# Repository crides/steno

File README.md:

# Steno

If you are here, you are probably looking for my embedded steno work. You can find the PCB design and production files for my steno keyboards (mostly known as the batwing or just bat) in the `pcb/` directory, and the embedded steno firmware (Kolibri) and the dictionary compiler in the `firmware/` and `compiler/` directories.

The detailed info for each can be found in their own READMEs, [boards](pcb/README.md) [firmware](firmware/README.md) and [dictionary compiler](compiler/README.md).

## What's Steno(graphy)?

If you don't know what stenography is, it's a short hand system primarily used by court reporters and captioners for note taking at a very high speeds. The English stenography system uses a special keyboard with only 23 keys on it, and the keys are meant to be pressed at the same time, producing combinations called chords. When combined together and translated through an engine, it can be used to input at very high speeds (professional stenographers need to reach above 225 wpm). Due to the price of commercial steno machines, free and open source alternatives started appearing, the most prominent among which is [Plover](https://github.com/openstenoproject/plover), which acts as a keyboard emulator that can translate chords from a \$20 gaming keyboard into words efficiently. A lot of ideas here are inspired by Plover.

If you want to go a bit more in depth, you should check out [this video](https://www.youtube.com/watch?v=JsRTTD9k2ME) by Aerick, or this [PyCon talk](https://www.youtube.com/watch?v=Wpv-Qb-dB6g) by Mirabai Knight, the creator of Plover.

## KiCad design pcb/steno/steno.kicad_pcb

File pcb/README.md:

# Embedded steno boards

These are the steno keyboards I designed and built, almost all of which has some form of hardware support for a embedded steno engine. These are just a list for more or less steno centric designs though, you can find my other boards using embedded steno like the [fissure v3](https://github.com/crides/fissure) and the [fusion](https://github.com/crides/fusion).

## Version 4

Version 4 is/are being designed as a more general board for others to use. There have been some people in the community requested me to sell some form of embedded steno board, and hardware vendors have yet to integrate the system (which on hardware is at least a flash chip). So these design(s) are meant to be easier to manufacture or assemble for the people printing their own.

## Version 3b / Bluebat

Picture from Jen/@sammdot: 

This is the screen testing platform for future designs with BLE versions of the bat. It was meant to compare the characteristics and power consumption of OLEDs, Eink display, Sharp memory display and the 2.2 inch LCD used in version 2 & 3. This version is not actually open sourced, as it was meant to simply be a personal testing board. The only reason it's here is because one was built for Jen/@sammdot as she requested one bat for polishing the UI (and the ATMega32u4 based ones, i.e. all previous versions, don't have enough flash for a good UI to be built without compromising other features).

## Version 3

Version 3 is the public testing version. This is done so that I can get more feedback from the community. This version uses basically the same design from version 2, but adopts a [raw screen module](https://www.aliexpress.com/item/32417585937.html) so that the cost of building is much cheaper. The other components are pushed to the back of the board as I imagine there wouldn't be much room at the front. This caused me a bit of trouble as I still want to put the diodes for the switches at the front, underneath the switches so that they are hidden. But that means I needed to hand solder the diodes while the other components are assembled at JLCPCB (they only support one sided assembly). As this was a public version, I changed the stagger of the keyboard to mimic that of Georgi's, but retained the relative position between thumbs and fingers (specifically thumb home and index home).

This version has been sent out to 9 other testers (I have one for testing) which helped me fix the dictionary downloader and polish the dictionary editing interface a bit more.

## Version 2

Version 2 is the one done as a class project (ECE445, Senior Project Labotory) and you can see the class number as a branch containing the work done there (it's been merged a long time ago of course). This is also the point where I ask the community for a name of the board, and that's where BatWings (or simply bat) comes from, from a suggestion by Jane/Germ/HardAsMagnets.

The main difference of this version is that it embeds the MCU onto the board itself (per course hardware requirements), includes a [much larger screen](https://www.adafruit.com/product/1480), and starts to use Bezier curves all over the board. Note that the one pictured is the first revision where the design is not electrically sound: I forgot a level shifter for the 5V MCU to interface with a 3.3V flash. This was not a problem before as the feather I was using runs the MCU at 3.3V and 8MHz. You could see the bodge wires under the screen if you look closely

This is also the point where me and my team added command formats so that the firmware can start to support a larger portion of Plover's builtin commands, and changed the dictionary format to a simpler and more regular one based on a single level of hashmap.

## Stenophone

This is a experimental version aimed to bring hardware steno to phones, so that one might be able to steno on the go (like on the bus, generally when you don't have a place to sit down). The idea is that you put this keyboard on the back of your phone, and your fingers reach to the back to press the keys, and your thumb will go over the phone to reach the vowels. This version is really only for testing out the idea, therefore a lot of the design aspects are still incomplete (for example see the battery location on the back). This version only differs in layout compare to the other ones, and uses the same steno firmware. It still uses BLE, as the plug on the phone will be simply blocked by hands.

## Version 1

Version 1 is a much better improvement over the first. This time I chose a split layout, but on the same board so I may use it on the go. The 2 halves are rotated 20 degrees each, so my hands won't have to bend much since it's not a actual split board. Like [my split keyboard](https://github.com/crides/fissure), this version also includes high levels of columnar stagger. I also put the MCU back to a normal position, so I don't have to worry about the underside of the keyboard anymore. This version also added a JST Li-ion battery plug (although in a weird position), a OLED for status display, a SOIC8 for experimenting with a QSPI flash, and a sdcard slot under the OLED screen.

Note the location of the sdcard; this is when it's not properly inserted to show the location. Also note the weirdly large battery and JST plug location.

## Version 0

The version 0 board is just a experimental board, with a small form factor while keeping the 11 column of keys needed. The number bar is missing, just like the Georgi, and the number keys are placed at either side of the vowels. As I was just starting to practice steno, I didn't know much about the dimension of a steno keyboard that I would feel comfortable using, so I simply used a ortholinear layout. In order to keep the form factor small, I tried to put the MCU under the PCB, so that it doesn't take any extra space on the PCB itself. But since I'm not used to doing that, it caused some issues when I later tried to modify the board and in normal usage.

Note the candy boxes I used to lift the board up so it's stable. Also note the sdcard slot and the bodges I did to accomodate the dictionary in the firmware.

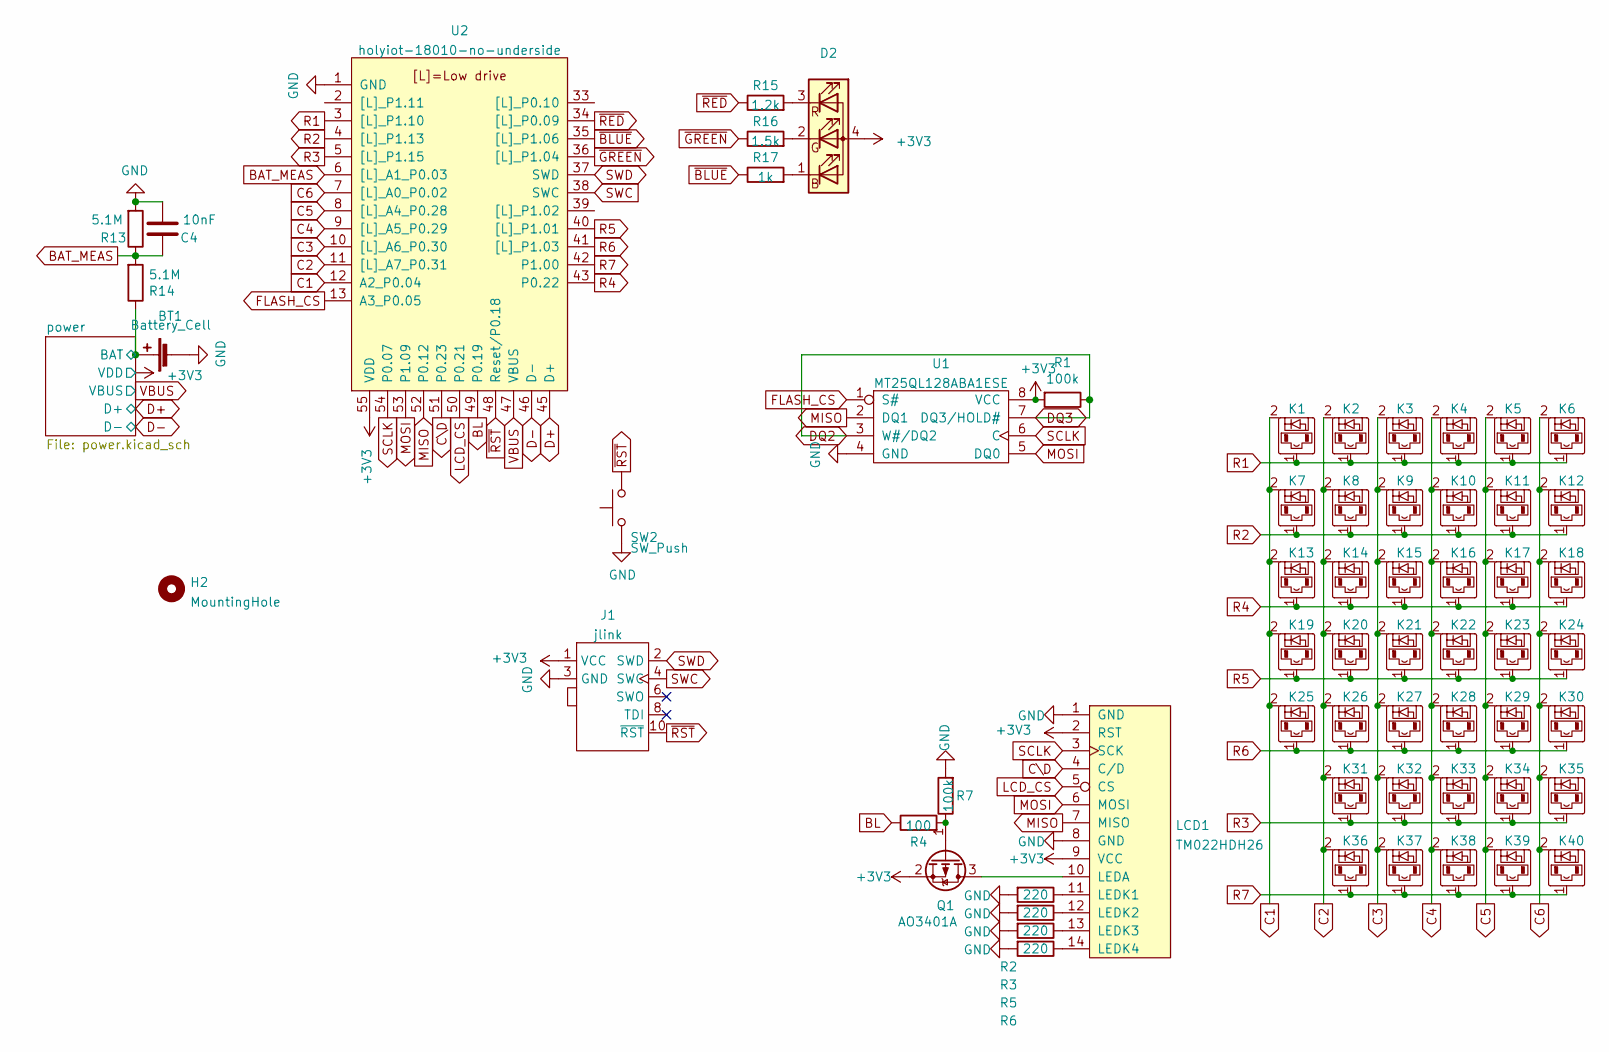
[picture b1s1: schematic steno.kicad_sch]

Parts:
BT1: Battery_Cell; JST_PH_S2B-PH-SM4-TB_1x02-1MP_P2.00mm_Horizontal
C4: 10nF; C_0603_1608Metric
D2: (no value)
H2: MountingHole; auklet-cover-mount
J1: jlink; PinHeader_2x05_P1.27mm_Vertical_SMD
K1, K2, K3, K4, K5, K6, K7, K8, K9, K10, K11, K12, K13, K14, K15, K16, K17, K18, K19, K20, K21, K22, K23, K24, K25, K26, K27, K28, K29, K30, K31, K32, K33, K34, K35, K36, K37, K38, K39, K40: diode-choc; pg1350-D
LCD1: TM022HDH26; TM022HDH26_back
Q1: AO3401A; SOT-23
R1, R7: 100k; R_0603_1608Metric
R2, R3, R5, R6: 220; R_0603_1608Metric
R4: 100; R_0603_1608Metric
R13, R14: 5.1M; R_0603_1608Metric
R15: 1.2k; R_0603_1608Metric
R16: 1.5k; R_0603_1608Metric
R17: 1k; R_0603_1608Metric
SW2: SW_Push; SW_SPST_TL3342
U1: MT25QL128ABA1ESE; SOIC-8_5.23x5.23mm_P1.27mm
U2: holyiot-18010-no-underside

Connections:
+3V3: D2.4 (A), J1.1 (VCC), LCD1.2 (RST), LCD1.9 (VCC), Q1.2 (S), R1.2, U1.8 (VCC), U2.55 (VDD); also elsewhere on the board
/power/BAT: BT1.1 (+), R14.1; also elsewhere on the board
BAT_MEAS: C4.1, R13.1, R14.2, U2.6 ([L]_A1_P0.03)
BL: R4.1, U2.49 (P0.19)
C1: K1.2, K7.2, K13.2, K19.2, K25.2, U2.12 (A2_P0.04)
C2: K2.2, K8.2, K14.2, K20.2, K26.2, K31.2, K36.2, U2.11 ([L]_A7_P0.31)
C3: K3.2, K9.2, K15.2, K21.2, K27.2, K32.2, K37.2, U2.10 ([L]_A6_P0.30)
C4: K4.2, K10.2, K16.2, K22.2, K28.2, K33.2, K38.2, U2.9 ([L]_A5_P0.29)
C5: K5.2, K11.2, K17.2, K23.2, K29.2, K34.2, K39.2, U2.8 ([L]_A4_P0.28)
C6: K6.2, K12.2, K18.2, K24.2, K30.2, K35.2, K40.2, U2.7 ([L]_A0_P0.02)
C\D: LCD1.4 (C/D), U2.51 (P0.23)
D+: U2.45 (D+); also elsewhere on the board
D-: U2.46 (D-); also elsewhere on the board
DQ2: R1.1, U1.3 (W#/DQ2), U1.7 (DQ3/HOLD#)
FLASH_CS: U1.1 (S#), U2.13 (A3_P0.05)
GND: BT1.2 (-), C4.2, J1.3 (GND), J1.5 (GND), LCD1.1 (GND), LCD1.8 (GND), R2.2, R3.2, R5.2, R6.2, R7.2, R13.2, SW2.1, U1.4 (GND), U2.1 (GND), U2.32 (GND), U2.44 (GND); also elsewhere on the board
LCD_CS: LCD1.5 (CS), U2.50 (P0.21)
MISO: LCD1.7 (MISO), U1.2 (DQ1), U2.52 (P0.12)
MOSI: LCD1.6 (MOSI), U1.5 (DQ0), U2.53 (P1.09)
unnamed: LCD1.10 (LEDA), Q1.3 (D)
unnamed: LCD1.11 (LEDK1), R2.1
unnamed: LCD1.12 (LEDK2), R3.1
unnamed: LCD1.13 (LEDK3), R5.1
unnamed: LCD1.14 (LEDK4), R6.1
unnamed: Q1.1 (G), R4.2, R7.1
unnamed: D2.3 (RK), R15.2
unnamed: D2.2 (GK), R16.2
unnamed: D2.1 (BK), R17.2
R1: K1.1, K2.1, K3.1, K4.1, K5.1, K6.1, U2.3 ([L]_P1.10)
R2: K7.1, K8.1, K9.1, K10.1, K11.1, K12.1, U2.4 ([L]_P1.13)
R3: K31.1, K32.1, K33.1, K34.1, K35.1, U2.5 ([L]_P1.15)
R4: K13.1, K14.1, K15.1, K16.1, K17.1, K18.1, U2.43 (P0.22)
R5: K19.1, K20.1, K21.1, K22.1, K23.1, K24.1, U2.40 ([L]_P1.01)
R6: K25.1, K26.1, K27.1, K28.1, K29.1, K30.1, U2.41 ([L]_P1.03)
R7: K36.1, K37.1, K38.1, K39.1, K40.1, U2.42 (P1.00)
SCLK: LCD1.3 (SCK), U1.6 (C), U2.54 (P0.07)
SWC: J1.4 (SWC), U2.38 (SWC)
SWD: J1.2 (SWD), U2.37 (SWD)
VBUS: U2.47 (VBUS); also elsewhere on the board
~BLUE: R17.1, U2.35 ([L]_P1.06)
~GREEN: R16.1, U2.36 ([L]_P1.04)
~RED: R15.1, U2.34 ([L]_P0.09)
~RST: J1.10 (~RST), SW2.2, U2.48 (Reset/P0.18)

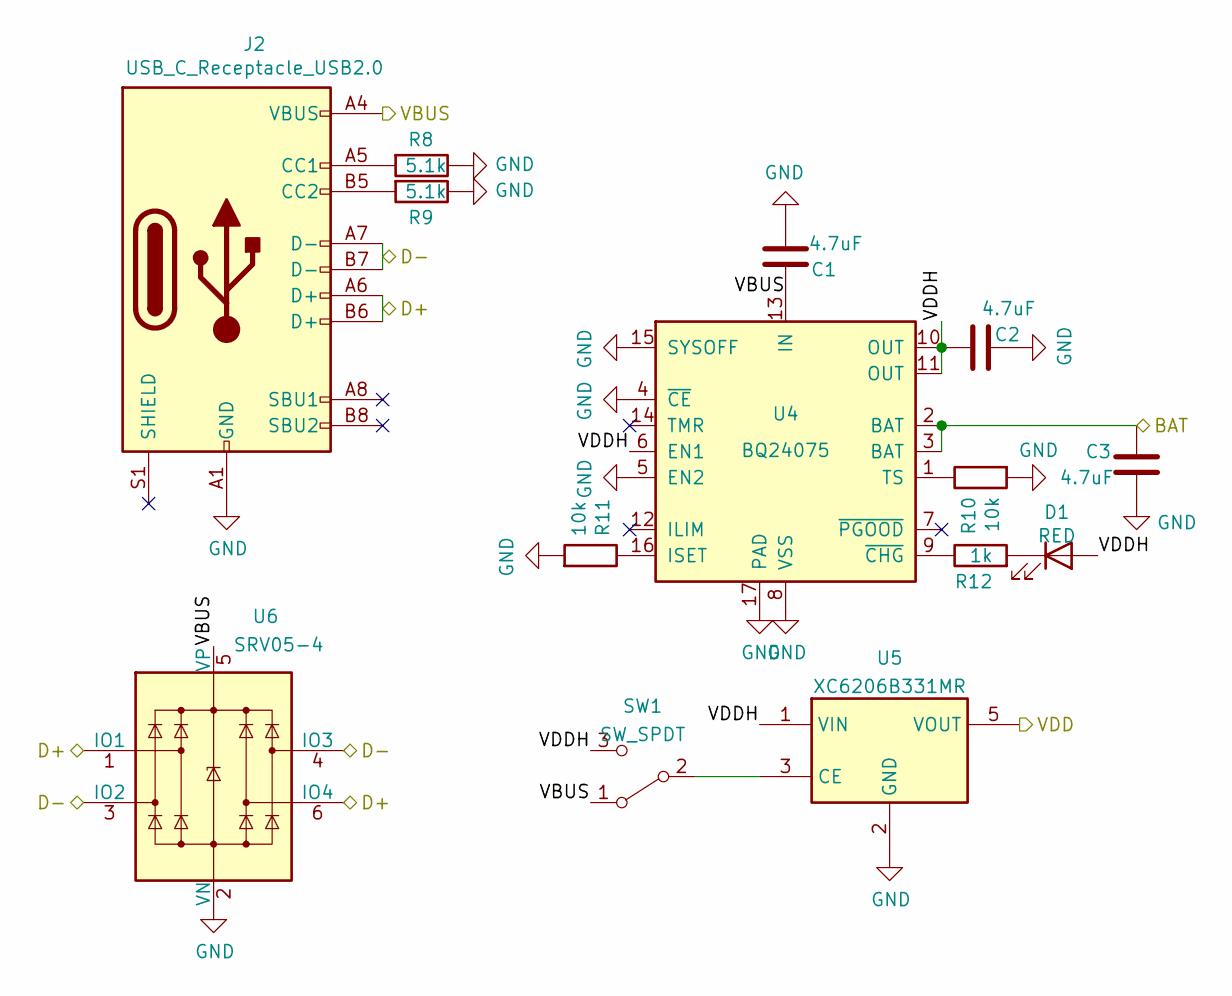
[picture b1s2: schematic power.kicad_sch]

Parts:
C1, C2, C3: 4.7uF; C_0603_1608Metric
D1: RED; LED_0805_2012Metric
J2: USB_C_Receptacle_USB2.0; USB_C_Receptacle_HRO_TYPE-C-31-M-12
R8, R9: 5.1k; R_0603_1608Metric
R10, R11: 10k; R_0603_1608Metric
R12: 1k; R_0603_1608Metric
SW1: SW_SPDT; SW_SPDT_PCM12
U4: BQ24075; VQFN-16-1EP_3x3mm_P0.5mm_EP1.68x1.68mm_ThermalVias
U5: XC6206B331MR; SOT-23-5
U6: SRV05-4; SOT-23-6

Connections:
+3V3: U5.5 (VOUT); also elsewhere on the board
/power/BAT: C3.1, U4.2 (BAT), U4.3 (BAT); also elsewhere on the board
/power/VDDH: C2.2, D1.2 (A), SW1.3 (C), U4.6 (EN1), U4.10 (OUT), U4.11 (OUT), U5.1 (VIN)
D+: J2.A6 (D+), J2.B6 (D+), U6.1 (IO1), U6.6 (IO4); also elsewhere on the board
D-: J2.A7 (D-), J2.B7 (D-), U6.3 (IO2), U6.4 (IO3); also elsewhere on the board
GND: C1.2, C2.1, C3.2, J2.A1 (GND), J2.A12 (GND), J2.B1 (GND), J2.B12 (GND), R8.1, R9.1, R10.2, R11.2, U4.4 (~CE), U4.5 (EN2), U4.8 (VSS), U4.15 (SYSOFF), U4.17 (PAD), U5.2 (GND), U6.2 (VN); also elsewhere on the board
unnamed: D1.1 (K), R12.2
unnamed: J2.A5 (CC1), R8.2
unnamed: J2.B5 (CC2), R9.2
unnamed: R10.1, U4.1 (TS)
unnamed: R11.1, U4.16 (ISET)
unnamed: R12.1, U4.9 (~CHG)
unnamed: SW1.2 (B), U5.3 (CE)
VBUS: C1.1, J2.A4 (VBUS), J2.A9 (VBUS), J2.B4 (VBUS), J2.B9 (VBUS), SW1.1 (A), U4.13 (IN), U6.5 (VP); also elsewhere on the board

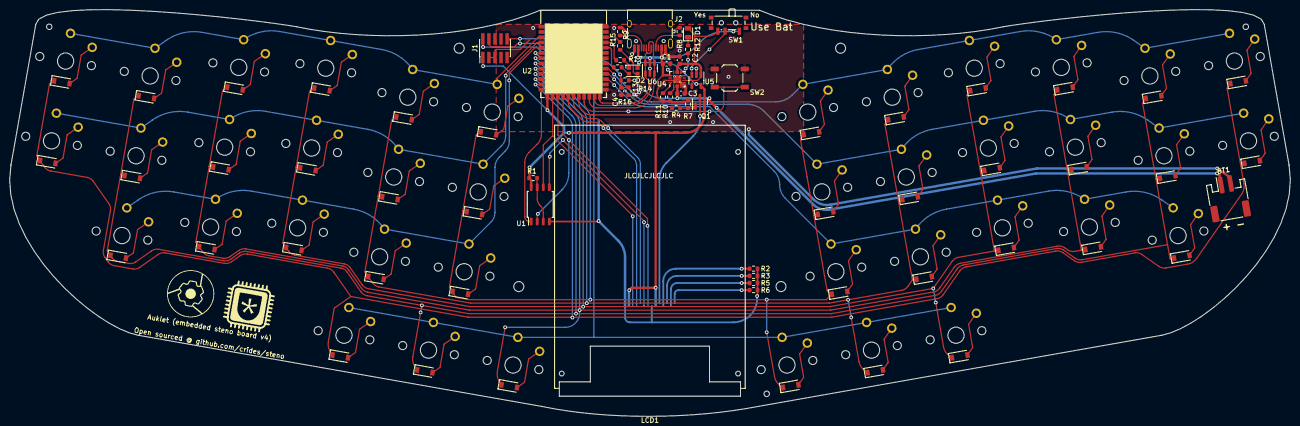
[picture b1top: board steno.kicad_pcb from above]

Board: 2 copper layers, 268.7 x 85.3 mm, 76 parts (0 on the bottom side), 51 nets.

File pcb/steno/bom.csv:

Comment,Designator,Footprint,LCSC
4.7uF,"C1,C2,C3",Capacitor_SMD:C_0603_1608Metric,
10nF,C4,Capacitor_SMD:C_0603_1608Metric,
RED,D1,LED_SMD:LED_0805_2012Metric,
LED_RABG,D2,LED_SMD:LED_ASMB-KTF0-0A306,C375569
MountingHole,H1,misc:auklet-mount,
MountingHole,H2,misc:auklet-cover-mount,
USB_C_Receptacle_USB2.0,J2,Connector_USB:USB_C_Receptacle_HRO_TYPE-C-31-M-12,
diode-choc,"K1,K2,K3,K4,K5,K6,K7,K8,K9,K10,K11,K12,K13,K14,K15,K16,K17,K18,K19,K20,K21,K22,K23,K24,K25,K26,K27,K28,K29,K30,K31,K32,K33,K34,K35,K36,K37,K38,K39,K40",pg1350:pg1350-D,C64898
AO3401A,Q1,Package_TO_SOT_SMD:SOT-23,
100k,"R1,R7",Resistor_SMD:R_0603_1608Metric,
220,"R2,R3,R5,R6",Resistor_SMD:R_0603_1608Metric,
100,R4,Resistor_SMD:R_0603_1608Metric,
5.1k,"R8,R9",Resistor_SMD:R_0603_1608Metric,
10k,"R10,R11",Resistor_SMD:R_0603_1608Metric,
1k,"R12,R17",Resistor_SMD:R_0603_1608Metric,
5.1M,"R13,R14",Resistor_SMD:R_0603_1608Metric,C13320
1.2k,R15,Resistor_SMD:R_0603_1608Metric,
1.5k,R16,Resistor_SMD:R_0603_1608Metric,
SW_SPDT,SW1,Button_Switch_SMD:SW_SPDT_PCM12,
SW_Push,SW2,Button_Switch_SMD:SW_SPST_TL3342,C318884
MT25QL128ABA1ESE,U1,Package_SO:SOIC-8_5.23x5.23mm_P1.27mm,
BQ24075,U4,Package_DFN_QFN:VQFN-16-1EP_3x3mm_P0.5mm_EP1.68x1.68mm_ThermalVias,
XC6206B331MR,U5,Package_TO_SOT_SMD:SOT-23-5,
SRV05-4,U6,Package_TO_SOT_SMD:SOT-23-6,

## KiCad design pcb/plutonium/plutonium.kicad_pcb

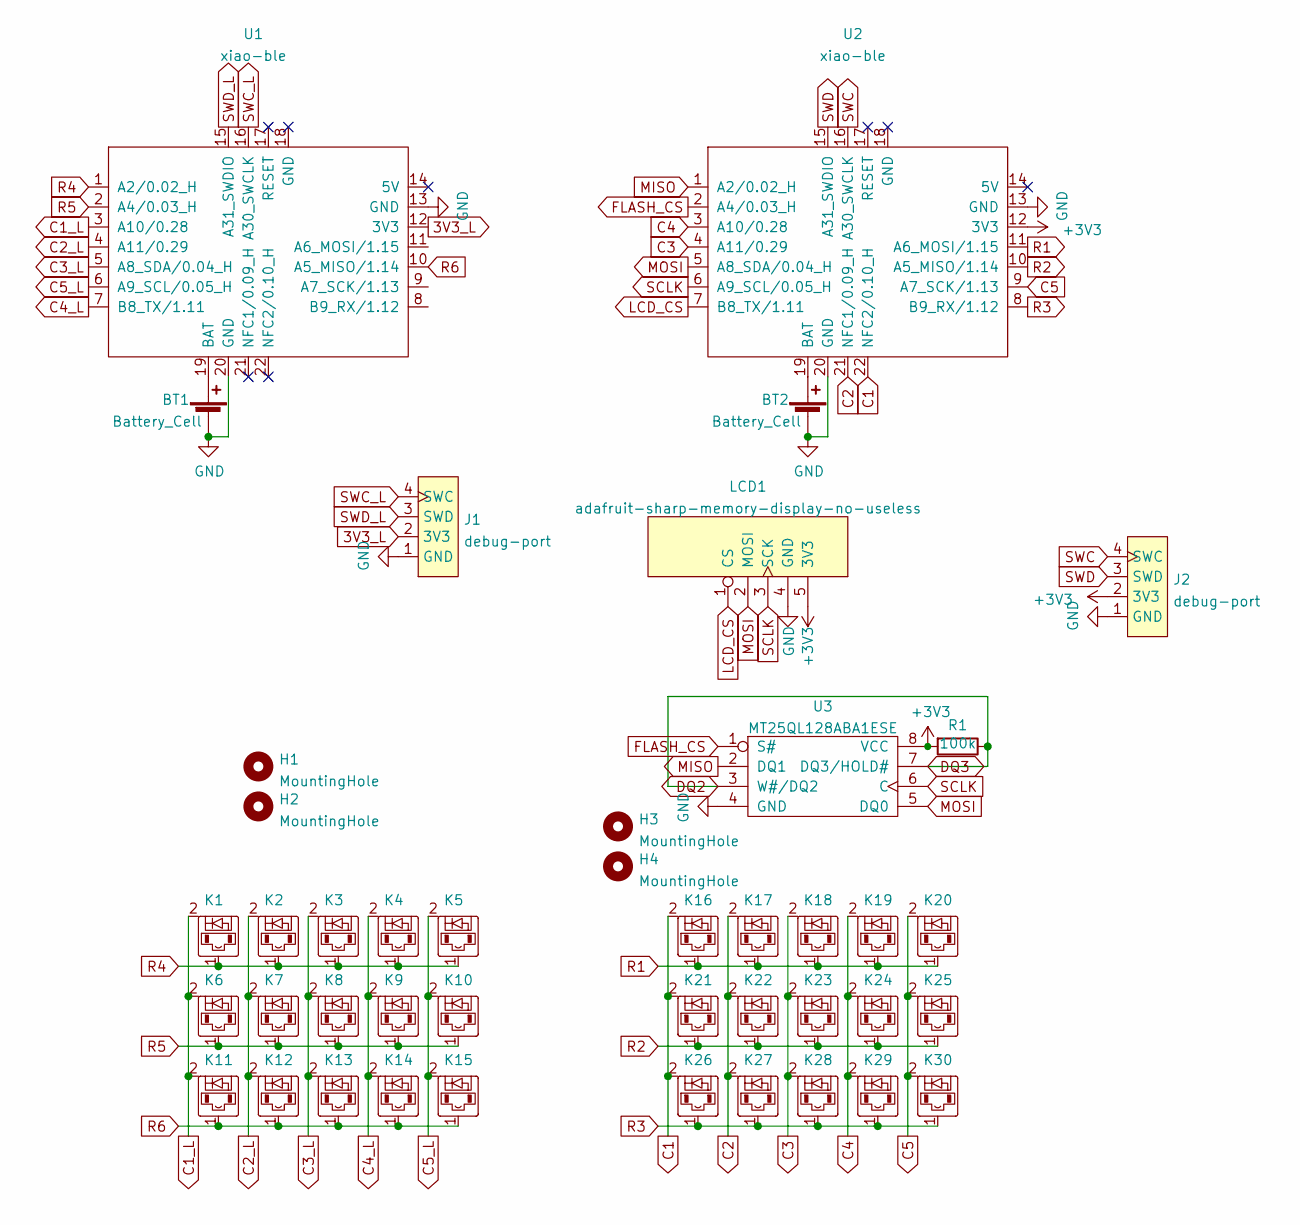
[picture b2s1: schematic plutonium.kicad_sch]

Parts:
BT1, BT2: Battery_Cell; JST_PH_S2B-PH-SM4-TB_1x02-1MP_P2.00mm_Horizontal
H1, H2, H3, H4: MountingHole; MountingHole_3.2mm_M3
J1, J2: debug-port; debug-port-single-side
K1, K2, K3, K4, K5, K6, K7, K8, K9, K10, K11, K12, K13, K14, K15, K16, K17, K18, K19, K20, K21, K22, K23, K24, K25, K26, K27, K28, K29, K30: diode-choc; pg1350-D
LCD1: adafruit-sharp-memory-display-no-useless; adafruit-sharp-memory-display-1.3in-no-mounting-no-useless
R1: 100k; R_0603_1608Metric
U1, U2: xiao-ble; xiao-ble-smd-cutout
U3: MT25QL128ABA1ESE; SOIC-8_5.23x5.23mm_P1.27mm

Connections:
3V3_L: J1.2 (3V3), U1.12 (3V3)
+3V3: J2.2 (3V3), LCD1.5 (3V3), R1.2, U2.12 (3V3), U3.8 (VCC)
C1: K16.2, K21.2, K26.2, U2.22 (NFC2/0.10_H)
C1_L: K1.2, K6.2, K11.2, U1.3 (A10/0.28)
C2: K17.2, K22.2, K27.2, U2.21 (NFC1/0.09_H)
C2_L: K2.2, K7.2, K12.2, U1.4 (A11/0.29)
C3: K18.2, K23.2, K28.2, U2.4 (A11/0.29)
C3_L: K3.2, K8.2, K13.2, U1.5 (A8_SDA/0.04_H)
C4: K19.2, K24.2, K29.2, U2.3 (A10/0.28)
C4_L: K4.2, K9.2, K14.2, U1.7 (B8_TX/1.11)
C5: K20.2, K25.2, K30.2, U2.9 (A7_SCK/1.13)
C5_L: K5.2, K10.2, K15.2, U1.6 (A9_SCL/0.05_H)
DQ2: R1.1, U3.3 (W#/DQ2), U3.7 (DQ3/HOLD#)
FLASH_CS: U2.2 (A4/0.03_H), U3.1 (S#)
GND: BT1.2 (-), BT2.2 (-), J1.1 (GND), J2.1 (GND), LCD1.4 (GND), U1.13 (GND), U1.20 (GND), U2.13 (GND), U2.20 (GND), U3.4 (GND)
LCD_CS: LCD1.1 (CS), U2.7 (B8_TX/1.11)
MISO: U2.1 (A2/0.02_H), U3.2 (DQ1)
MOSI: LCD1.2 (MOSI), U2.5 (A8_SDA/0.04_H), U3.5 (DQ0)
unnamed: BT1.1 (+), U1.19 (BAT)
unnamed: BT2.1 (+), U2.19 (BAT)
R1: K16.1, K17.1, K18.1, K19.1, K20.1, U2.11 (A6_MOSI/1.15)
R2: K21.1, K22.1, K23.1, K24.1, K25.1, U2.10 (A5_MISO/1.14)
R3: K26.1, K27.1, K28.1, K29.1, K30.1, U2.8 (B9_RX/1.12)
R4: K1.1, K2.1, K3.1, K4.1, K5.1, U1.1 (A2/0.02_H)
R5: K6.1, K7.1, K8.1, K9.1, K10.1, U1.2 (A4/0.03_H)
R6: K11.1, K12.1, K13.1, K14.1, K15.1, U1.10 (A5_MISO/1.14)
SCLK: LCD1.3 (SCK), U2.6 (A9_SCL/0.05_H), U3.6 (C)
SWC: J2.4 (SWC), U2.16 (A30_SWCLK)
SWC_L: J1.4 (SWC), U1.16 (A30_SWCLK)
SWD: J2.3 (SWD), U2.15 (A31_SWDIO)
SWD_L: J1.3 (SWD), U1.15 (A31_SWDIO)

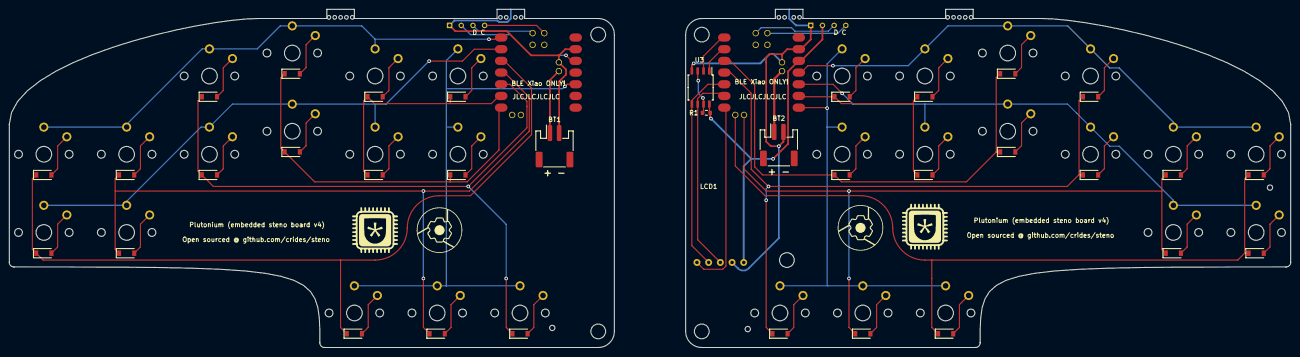
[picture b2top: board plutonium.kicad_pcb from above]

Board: 2 copper layers, 278.5 x 73.5 mm, 43 parts (0 on the bottom side), 31 nets.

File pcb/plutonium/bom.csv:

Comment,Designator,Footprint,LCSC
diode-choc,"K1,K2,K3,K4,K5,K6,K7,K8,K9,K10,K11,K12,K13,K14,K15,K16,K17,K18,K19,K20,K21,K22,K23,K24,K25,K26,K27,K28,K29,K30",pg1350:pg1350-D,C64898
100k,R1,Resistor_SMD:R_0603_1608Metric,
MT25QL128ABA1ESE,U3,Package_SO:SOIC-8_5.23x5.23mm_P1.27mm,C97521

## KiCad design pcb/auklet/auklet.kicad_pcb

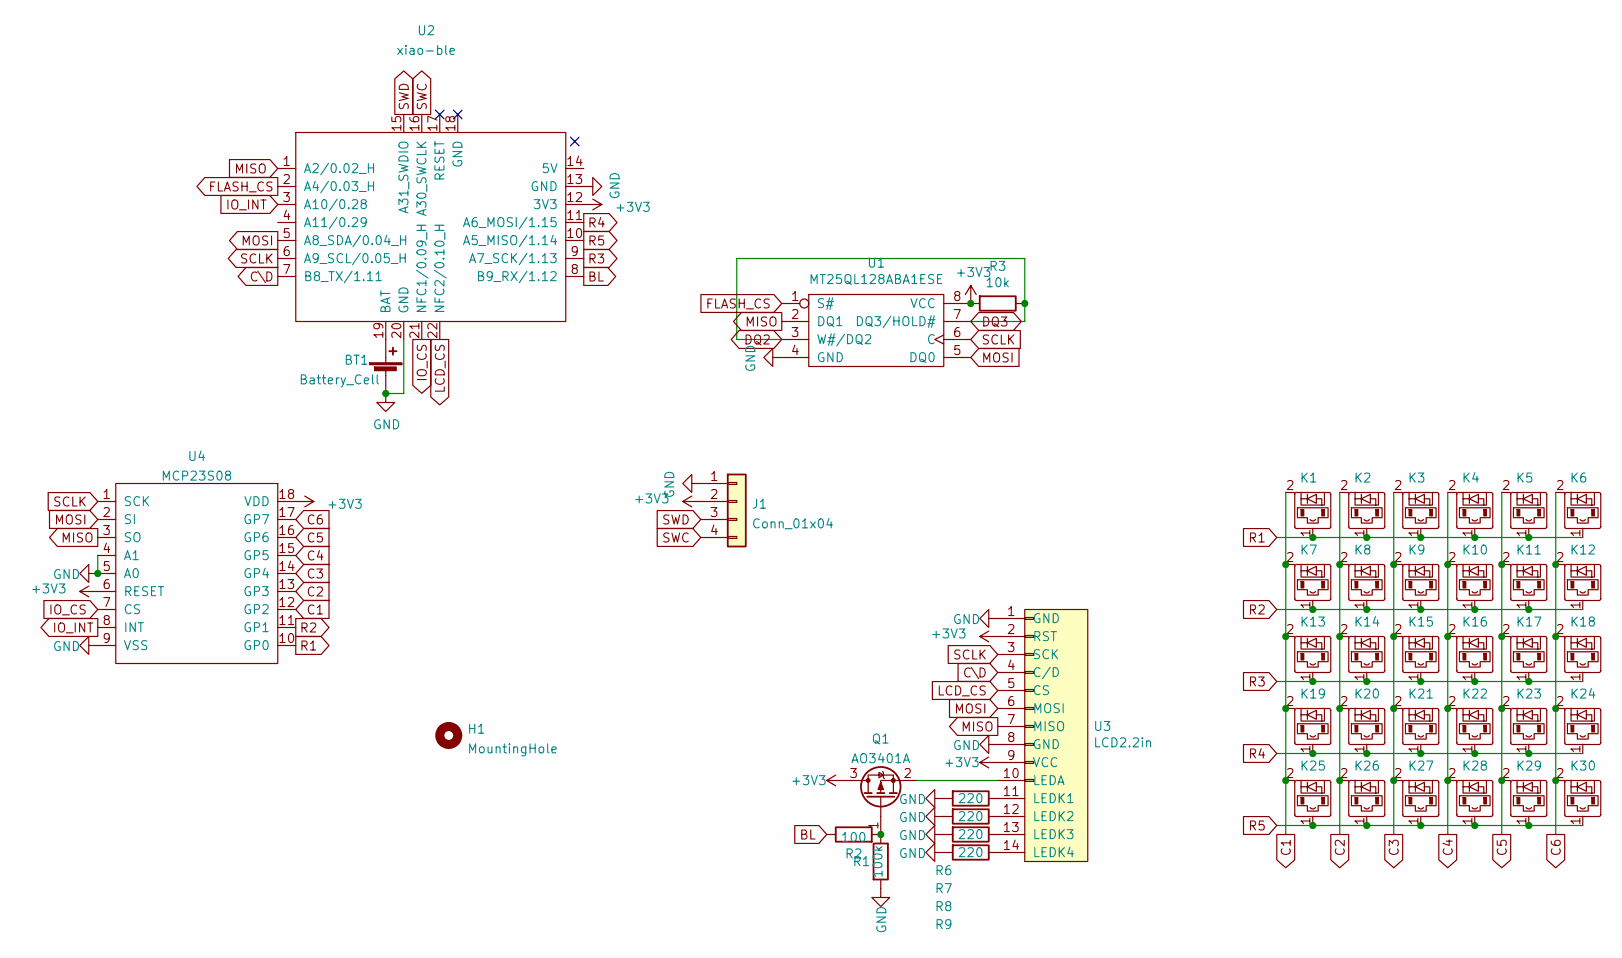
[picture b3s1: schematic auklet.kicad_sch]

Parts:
BT1: Battery_Cell; JST_PH_S2B-PH-SM4-TB_1x02-1MP_P2.00mm_Horizontal
H1: MountingHole; auklet-mount
J1: Conn_01x04; debug-port-single-side
K1, K2, K3, K4, K5, K6, K7, K8, K9, K10, K11, K12, K13, K14, K15, K16, K17, K18, K19, K20, K21, K22, K23, K24, K25, K26, K27, K28, K29, K30: diode-choc; pg1350-D
Q1: AO3401A; SOT-23
R1: 100k; R_0603_1608Metric
R2: 100; R_0603_1608Metric
R3: 10k; R_0603_1608Metric
R6, R7, R8, R9: 220; R_0603_1608Metric
U1: MT25QL128ABA1ESE; SOP-8_5.28x5.23mm_P1.27mm
U2: xiao-ble; xiao-ble-smd
U3: LCD2.2in; TM022HDH26
U4: MCP23S08; SOIC-18W_7.5x11.6mm_P1.27mm

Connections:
+3V3: J1.2, Q1.3 (D), R3.2, U1.8 (VCC), U2.12 (3V3), U3.2 (RST), U3.9 (VCC), U4.6 (RESET), U4.18 (VDD)
BL: R2.1, U2.8 (B9_RX/1.12)
C1: K1.2, K7.2, K13.2, K19.2, K25.2, U4.12 (GP2)
C2: K2.2, K8.2, K14.2, K20.2, K26.2, U4.13 (GP3)
C3: K3.2, K9.2, K15.2, K21.2, K27.2, U4.14 (GP4)
C4: K4.2, K10.2, K16.2, K22.2, K28.2, U4.15 (GP5)
C5: K5.2, K11.2, K17.2, K23.2, K29.2, U4.16 (GP6)
C6: K6.2, K12.2, K18.2, K24.2, K30.2, U4.17 (GP7)
C\D: U2.7 (B8_TX/1.11), U3.4 (C/D)
DQ2: R3.1, U1.3 (W#/DQ2), U1.7 (DQ3/HOLD#)
FLASH_CS: U1.1 (S#), U2.2 (A4/0.03_H)
GND: BT1.2 (-), J1.1, R1.2, R6.2, R7.2, R8.2, R9.2, U1.4 (GND), U2.13 (GND), U2.20 (GND), U3.1 (GND), U3.8 (GND), U4.4 (A1), U4.5 (A0), U4.9 (VSS)
IO_CS: U2.21 (NFC1/0.09_H), U4.7 (CS)
IO_INT: U2.3 (A10/0.28), U4.8 (INT)
LCD_CS: U2.22 (NFC2/0.10_H), U3.5 (CS)
MISO: U1.2 (DQ1), U2.1 (A2/0.02_H), U3.7 (MISO), U4.3 (SO)
MOSI: U1.5 (DQ0), U2.5 (A8_SDA/0.04_H), U3.6 (MOSI), U4.2 (SI)
unnamed: BT1.1 (+), U2.19 (BAT)
unnamed: Q1.1 (G), R1.1, R2.2
unnamed: Q1.2 (S), U3.10 (LEDA)
unnamed: R6.1, U3.11 (LEDK1)
unnamed: R7.1, U3.12 (LEDK2)
unnamed: R8.1, U3.13 (LEDK3)
unnamed: R9.1, U3.14 (LEDK4)
R1: K1.1, K2.1, K3.1, K4.1, K5.1, K6.1, U4.10 (GP0)
R2: K7.1, K8.1, K9.1, K10.1, K11.1, K12.1, U4.11 (GP1)
R3: K13.1, K14.1, K15.1, K16.1, K17.1, K18.1, U2.9 (A7_SCK/1.13)
R4: K19.1, K20.1, K21.1, K22.1, K23.1, K24.1, U2.11 (A6_MOSI/1.15)
R5: K25.1, K26.1, K27.1, K28.1, K29.1, K30.1, U2.10 (A5_MISO/1.14)
SCLK: U1.6 (C), U2.6 (A9_SCL/0.05_H), U3.3 (SCK), U4.1 (SCK)
SWC: J1.4, U2.16 (A30_SWCLK)
SWD: J1.3, U2.15 (A31_SWDIO)

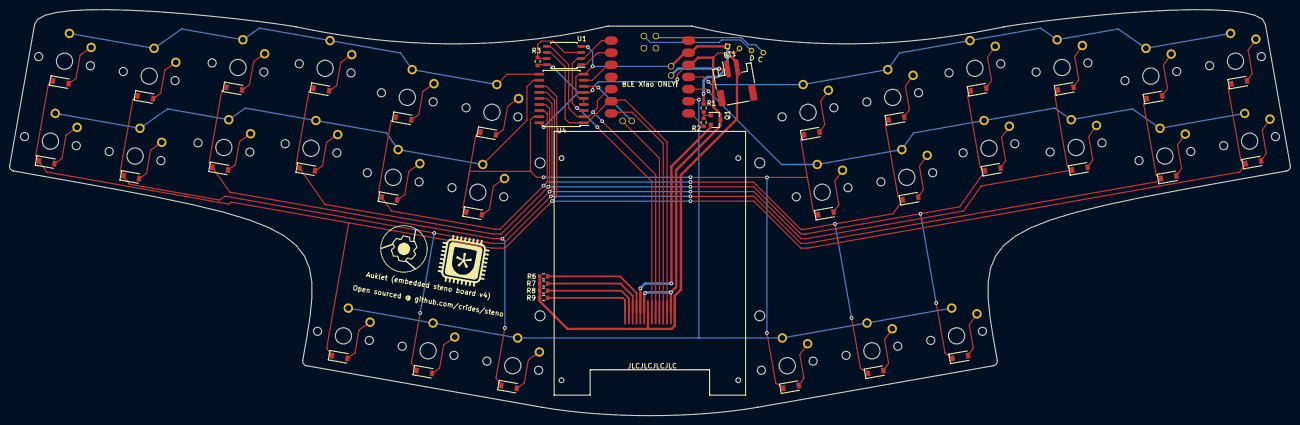
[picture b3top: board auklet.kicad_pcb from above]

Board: 2 copper layers, 268.1 x 85.0 mm, 45 parts (0 on the bottom side), 32 nets.

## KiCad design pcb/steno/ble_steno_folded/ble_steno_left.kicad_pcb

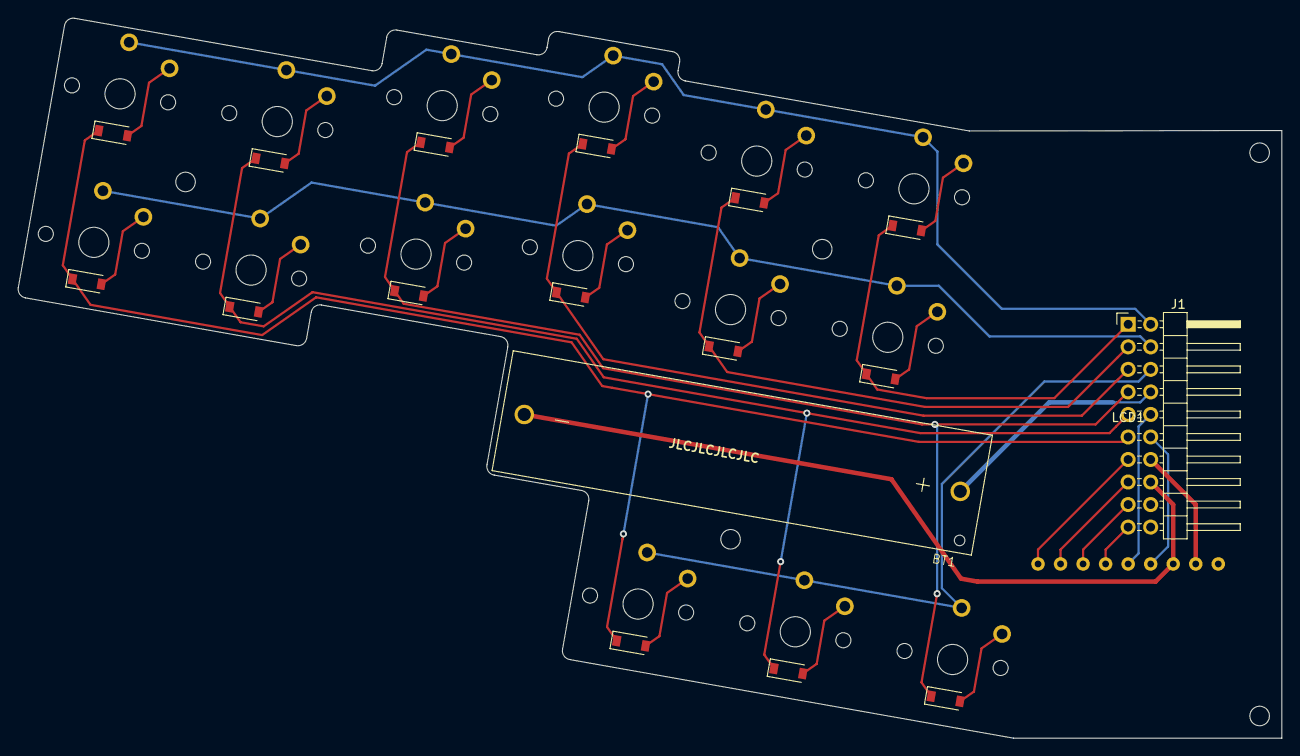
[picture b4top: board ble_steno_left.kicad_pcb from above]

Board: 2 copper layers, 142.5 x 81.2 mm, 18 parts (0 on the bottom side), 18 nets.

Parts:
BT1: Battery_Cell; BA1AAAPC
J1: Conn_02x10_Odd_Even; PinHeader_2x10_P2.54mm_Horizontal
K1, K2, K3, K4, K5, K6, K7, K8, K9, K10, K11, K12, K13, K14, K15: 1N4148W; PG1350
LCD1: SHARP_LCD; Adafruit_Sharp_Memory_Display_1.3in_no_mounting

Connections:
+3V3: J1.14, LCD1.8
BAT: BT1.1, J1.8
COL1: J1.11, K1.2, K7.2, K13.2
COL2: J1.9, K2.2, K8.2, K14.2
COL3: J1.7, K3.2, K9.2, K15.2
COL4: J1.5, K4.2, K10.2
COL5: J1.3, K5.2, K11.2
COL6: J1.1, K6.2, K12.2
DISP: J1.15, LCD1.2
EIN: J1.13, LCD1.1
EMD: J1.17, LCD1.3
GND: BT1.2, J1.16, LCD1.7
LCD_CS: J1.19, LCD1.4
MOSI: J1.10, LCD1.5
ROW1: J1.2, K1.1, K2.1, K3.1, K4.1, K5.1, K6.1
ROW2: J1.4, K7.1, K8.1, K9.1, K10.1, K11.1, K12.1
ROW3: J1.6, K13.1, K14.1, K15.1
SCK: J1.12, LCD1.6

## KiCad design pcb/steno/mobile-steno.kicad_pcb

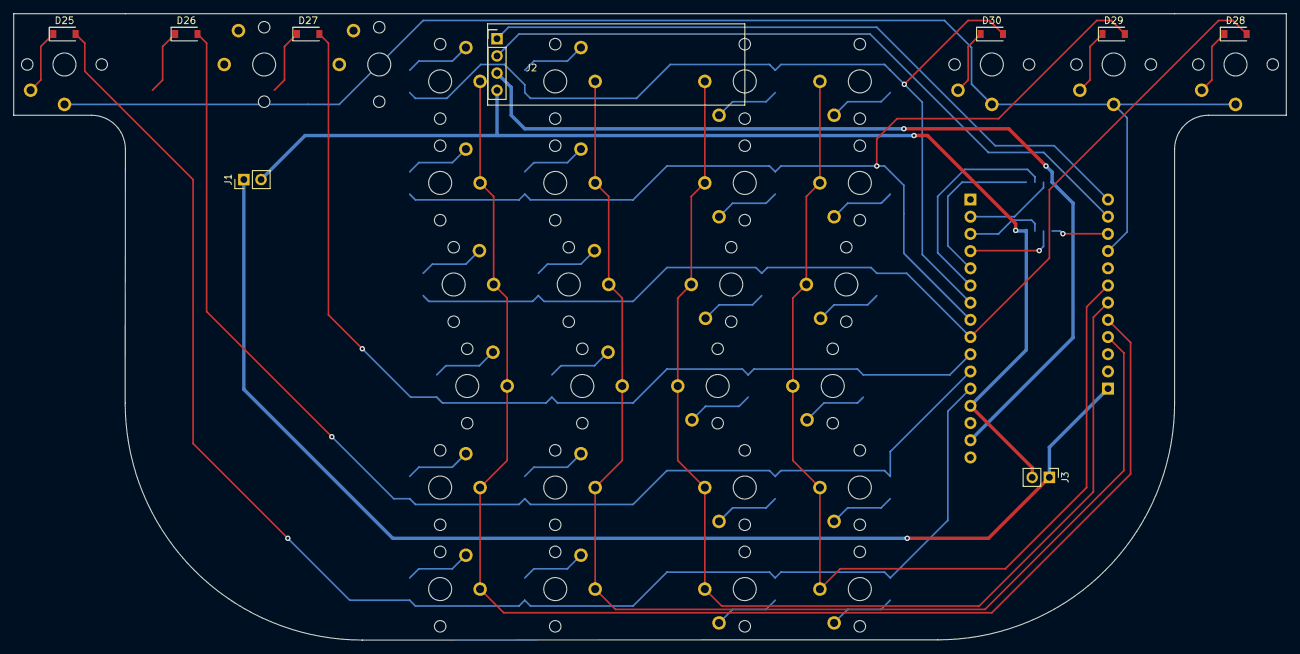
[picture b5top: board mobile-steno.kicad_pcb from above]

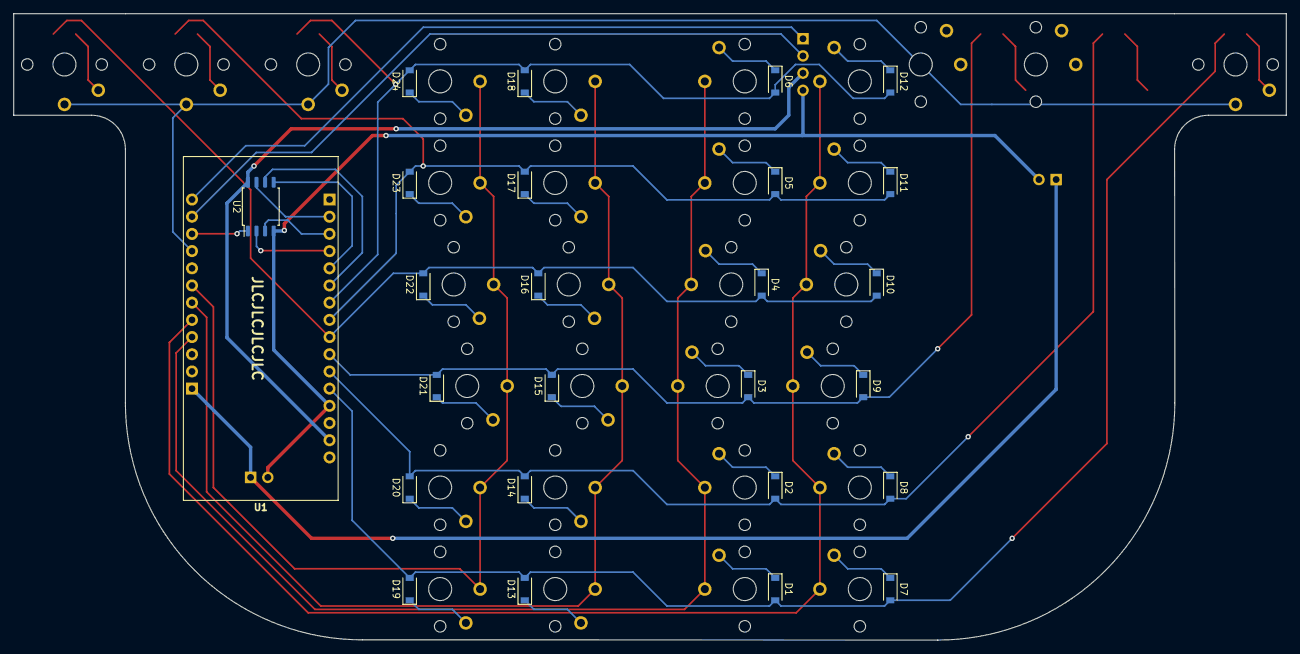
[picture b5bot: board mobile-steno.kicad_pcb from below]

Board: 2 copper layers, 188.0 x 92.5 mm, 65 parts (50 on the bottom side), 52 nets.

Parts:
D1, D2, D3, D4, D5, D6, D7, D8, D9, D10, D11, D12, D13, D14, D15, D16, D17, D18, D19, D20, D21, D22, D23, D24, D25, D26, D27, D28, D29, D30: DIODE; D_SOD-123
J1, J3: Conn_01x02; PinHeader_1x02_P2.54mm_Vertical
J2: Conn_01x04; OLED
K1, K2, K3, K4, K5, K6, K7, K8, K9, K10, K11, K12, K13, K14, K15, K16, K17, K18, K19, K20, K21, K22, K23, K24, K25, K26, K27, K28, K29, K30: KEYSW; Kailh-PG1350-1u-No-Clickhole
U1: Adafruit_Feather; ADAFRUIT_FEATHER
U2: MT25QL128ABA1ESE; SOP-8_5.28x5.23mm_P1.27mm

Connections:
BAT: J1.1, J3.1, U1.17
COL1: D1.2, D7.2, D13.2, D19.2, D25.2, U1.12
COL2: D2.2, D8.2, D14.2, D20.2, D26.2, U1.11
COL3: D3.2, D9.2, D15.2, D21.2, D27.2, U1.10
COL4: D4.2, D10.2, D16.2, D22.2, D28.2, U1.9
COL5: D5.2, D11.2, D17.2, D23.2, D29.2, U1.8
COL6: D6.2, D12.2, D18.2, D24.2, D30.2, U1.7
CS: U1.26, U2.1
DQ2: U1.3, U2.3
DQ3: U1.2, U2.7
GND: J1.2, J2.4, J3.2, U1.13, U2.4
MISO_DQ1: U1.4, U2.2
MOSI_DQ0: U1.5, U2.5
unnamed: D1.1, K1.2
unnamed: D2.1, K2.2
unnamed: D3.1, K3.2
unnamed: D4.1, K4.2
unnamed: D5.1, K5.2
unnamed: D6.1, K6.2
unnamed: D7.1, K7.2
unnamed: D8.1, K8.2
unnamed: D9.1, K9.2
unnamed: D10.1, K10.2
unnamed: D11.1, K11.2
unnamed: D12.1, K12.2
unnamed: D13.1, K13.2
unnamed: D14.1, K14.2
unnamed: D15.1, K15.2
unnamed: D16.1, K16.2
unnamed: D17.1, K17.2
unnamed: D18.1, K18.2
unnamed: D19.1, K19.2
unnamed: D20.1, K20.2
unnamed: D21.1, K21.2
unnamed: D22.1, K22.2
unnamed: D23.1, K23.2
unnamed: D24.1, K24.2
unnamed: D25.1, K25.2
unnamed: D26.1, K26.2
unnamed: D27.1, K27.2
unnamed: D28.1, K28.2
unnamed: D29.1, K29.2
unnamed: D30.1, K30.2
ROW1: K1.1, K2.1, K3.1, K4.1, K5.1, K6.1, U1.20
ROW2: K7.1, K8.1, K9.1, K10.1, K11.1, K12.1, U1.21
ROW3: K13.1, K14.1, K15.1, K16.1, K17.1, K18.1, U1.22
ROW4: K19.1, K20.1, K21.1, K22.1, K23.1, K24.1, U1.23
ROW5: K25.1, K26.1, K27.1, K28.1, K29.1, K30.1, U1.25
SCL: J2.2, U1.27
SCLK: U1.6, U2.6
SDA: J2.1, U1.28
VCC: J2.3, U1.15, U2.8
